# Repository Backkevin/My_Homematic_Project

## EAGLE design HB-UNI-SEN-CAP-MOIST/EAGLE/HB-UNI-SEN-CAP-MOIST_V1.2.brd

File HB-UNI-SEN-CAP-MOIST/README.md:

# HB-UNI-SEN-CAP-MOIST

+ HB-UNI-SEN-CAP-MOIST
    + V1.2
		* Work 75%
		* 230VAC Version
		* Partlist not OK
	+ V0.5
		* Work 25%
		* Solar Version
		* Partlist not OK
	+ Work in progress !
>

### Partslist 230VAC Version
                    
  Part Name   |      PIC      |   Part Info   | Part Quantity |   Part Link 
------------- | ------------- | ------------- | ------------- | -------------
Arduino||Arduino Pro Mini 8Mhz 3.3V|1|[Links](https://de.aliexpress.com/item/32863952987.html?spm=a2g0s.9042311.0.0.27424c4d2YDzey)
CC1101||CC1101 Funkmodul|1|[Links](https://de.aliexpress.com/item/32924239954.html?spm=a2g0s.9042311.0.0.27424c4dO9ofu2)
Config,S1 - S4||Taster 6x6|5|[Links](https://de.aliexpress.com/item/32912263133.html?spm=a2g0s.9042311.0.0.2cb44c4dtuowdv)
LED1||LED 3mm|1|[Links](https://de.aliexpress.com/item/32844298998.html?spm=a2g0s.9042311.0.0.27424c4dBW9kvr)
HLK-5M05||HLK-PM01|1|[Links](https://de.aliexpress.com/item/32705471039.html?spm=a2g0s.9042311.0.0.2cb44c4dtuowdv)
F1,F2||Sicherungshalter|2|[Links](https://de.aliexpress.com/item/32817849786.html?spm=a2g0o.productlist.0.0.260073beDSkClD&algo_pvid=51b52a6f-dc94-4152-9721-98bffea40076&algo_expid=51b52a6f-dc94-4152-9721-98bffea40076-1&btsid=c94e558f-368d-470b-a49c-61c69230d3d9&ws_ab_test=searchweb0_0,searchweb201602_2,searchweb201603_52)
R1 - R5||470 Ohm Widerstand|5|[Links](https://de.aliexpress.com/item/32475181535.html?spm=a2g0o.productlist.0.0.d4fa8034p2AKck&s=p&algo_pvid=4976c9e3-6165-4df4-b127-6d9845fdbe12&algo_expid=4976c9e3-6165-4df4-b127-6d9845fdbe12-1&btsid=7a52ff49-9ff4-47d2-965f-007ad481e8b7&ws_ab_test=searchweb0_0,searchweb201602_2,searchweb201603_52)
230V,S1 - S4||Wannenstecker für AKL 249, 2-pol, RM5,08|5|[Links](https://www.reichelt.de/wannenstecker-fuer-akl-249-2-pol-rm5-08-akl-230-02-p36701.html?)
RL1 - RL4||Wannenstecker für AKL 249, 3-pol, RM5,08|4|[Links](https://www.reichelt.de/wannenstecker-fuer-akl-249-3-pol-rm5-08-akl-230-03-p36702.html?)
Arduino||Pin Header Streifen 12 Pin|2|[Links](https://de.aliexpress.com/item/32904918519.html?spm=a2g0s.9042311.0.0.27424c4dCsKCBi)
CC1101||Stiftleiste 20 polig, vergoldet, Raster 2,00mm|1|[Links](https://secure.reichelt.com/lu/de/stiftleiste-20-pol-vergoldet-bkl-10120400-p235635.html?)
C1||50V10UF|1|[Links](https://de.aliexpress.com/item/32741687066.html?spm=a2g0o.productlist.0.0.4d225216N68Cr1&algo_pvid=dbcb75f4-e623-4355-8aa4-ccd3a7b65d32&algo_expid=dbcb75f4-e623-4355-8aa4-ccd3a7b65d32-3&btsid=a9b8176e-1372-45d7-a781-8d3fc9fab8e5&ws_ab_test=searchweb0_0,searchweb201602_2,searchweb201603_52)
Arduino||Jumper|1|[Links](https://de.aliexpress.com/item/32873263301.html?spm=a2g0o.productlist.0.0.18ea263dluRsmQ&algo_pvid=b495ebad-e4de-4809-a086-8143c1f9f12b&algo_expid=b495ebad-e4de-4809-a086-8143c1f9f12b-2&btsid=53bb7c29-6fd7-4471-b8c4-bc2766b36d10&ws_ab_test=searchweb0_0,searchweb201602_2,searchweb201603_52)
-|-|-|-
-||Feuchtigkeit Sensor|7|[Links](https://de.aliexpress.com/item/32892951369.html?spm=a2g0s.9042311.0.0.27424c4dkyqylL)
OPTIONAL||FT232RL USB zu TTL Serielle Adapter|1|[Links](https://de.aliexpress.com/item/32846166237.html?spm=a2g0s.9042311.0.0.27424c4dQGznlY)

>

### Partslist Solar Version
                    
  Part Name   |      PIC      |   Part Info   | Part Quantity |   Part Link 
------------- | ------------- | ------------- | ------------- | -------------
-||Arduino Pro Mini 8Mhz 3.3V|1|[Links](https://de.aliexpress.com/item/32863952987.html?spm=a2g0s.9042311.0.0.27424c4d2YDzey)
-||CC1101 Funkmodul|1|[Links](https://de.aliexpress.com/item/32924239954.html?spm=a2g0s.9042311.0.0.27424c4dO9ofu2)
Config||Taster 6x6|1|[Links](https://de.aliexpress.com/item/32912263133.html?spm=a2g0s.9042311.0.0.2cb44c4dtuowdv)
LED1||LED 3mm|1|[Links](https://de.aliexpress.com/item/32844298998.html?spm=a2g0s.9042311.0.0.27424c4dBW9kvr)
R1||470 Ohm Widerstand|1|[Links]()
Arduino||Pin Header Streifen 12 Pin|2|[Links](https://de.aliexpress.com/item/32904918519.html?spm=a2g0s.9042311.0.0.27424c4dCsKCBi)
CC1101||Stiftleiste 20 polig, vergoldet, Raster 2,00mm|1|[Links](https://secure.reichelt.com/lu/de/stiftleiste-20-pol-vergoldet-bkl-10120400-p235635.html?)
C1||50V10UF|1|[Links](https://de.aliexpress.com/item/32741687066.html?spm=a2g0o.productlist.0.0.4d225216N68Cr1&algo_pvid=dbcb75f4-e623-4355-8aa4-ccd3a7b65d32&algo_expid=dbcb75f4-e623-4355-8aa4-ccd3a7b65d32-3&btsid=a9b8176e-1372-45d7-a781-8d3fc9fab8e5&ws_ab_test=searchweb0_0,searchweb201602_2,searchweb201603_52)
Sabotage,Arduino||Jumper|1|[Links](https://de.aliexpress.com/item/32873263301.html?spm=a2g0o.productlist.0.0.18ea263dluRsmQ&algo_pvid=b495ebad-e4de-4809-a086-8143c1f9f12b&algo_expid=b495ebad-e4de-4809-a086-8143c1f9f12b-2&btsid=53bb7c29-6fd7-4471-b8c4-bc2766b36d10&ws_ab_test=searchweb0_0,searchweb201602_2,searchweb201603_52)
-||Ladegerät 5V|1|[Links](https://de.aliexpress.com/item/32816412117.html?spm=a2g0s.9042311.0.0.75df4c4dhlR1XP)
-||LiPo Protect|1|[Links](https://de.aliexpress.com/item/32816412117.html?spm=a2g0s.9042311.0.0.75df4c4dhlR1XP)
-||Lipo Batterie 3,7 V 800 mah|1|[Links](https://de.aliexpress.com/item/32884273792.html?spm=a2g0s.9042311.0.0.27424c4dkyqylL)
-||Solar Panel 6 V 2 W 0.35A|1|[Links](https://de.aliexpress.com/item/32955737209.html?spm=a2g0s.9042311.0.0.27424c4dBO3PxC)
-||SMA buchse Adapter|1|[Links](https://de.aliexpress.com/item/32876812319.html?spm=a2g0s.9042311.0.0.27424c4dkyqylL)
-|-|-|-
-||Feuchtigkeit Sensor|7|[Links](https://de.aliexpress.com/item/32892951369.html?spm=a2g0s.9042311.0.0.27424c4dkyqylL)
OPTIONAL||FT232RL USB zu TTL Serielle Adapter|1|[Links](https://de.aliexpress.com/item/32846166237.html?spm=a2g0s.9042311.0.0.27424c4dQGznlY)

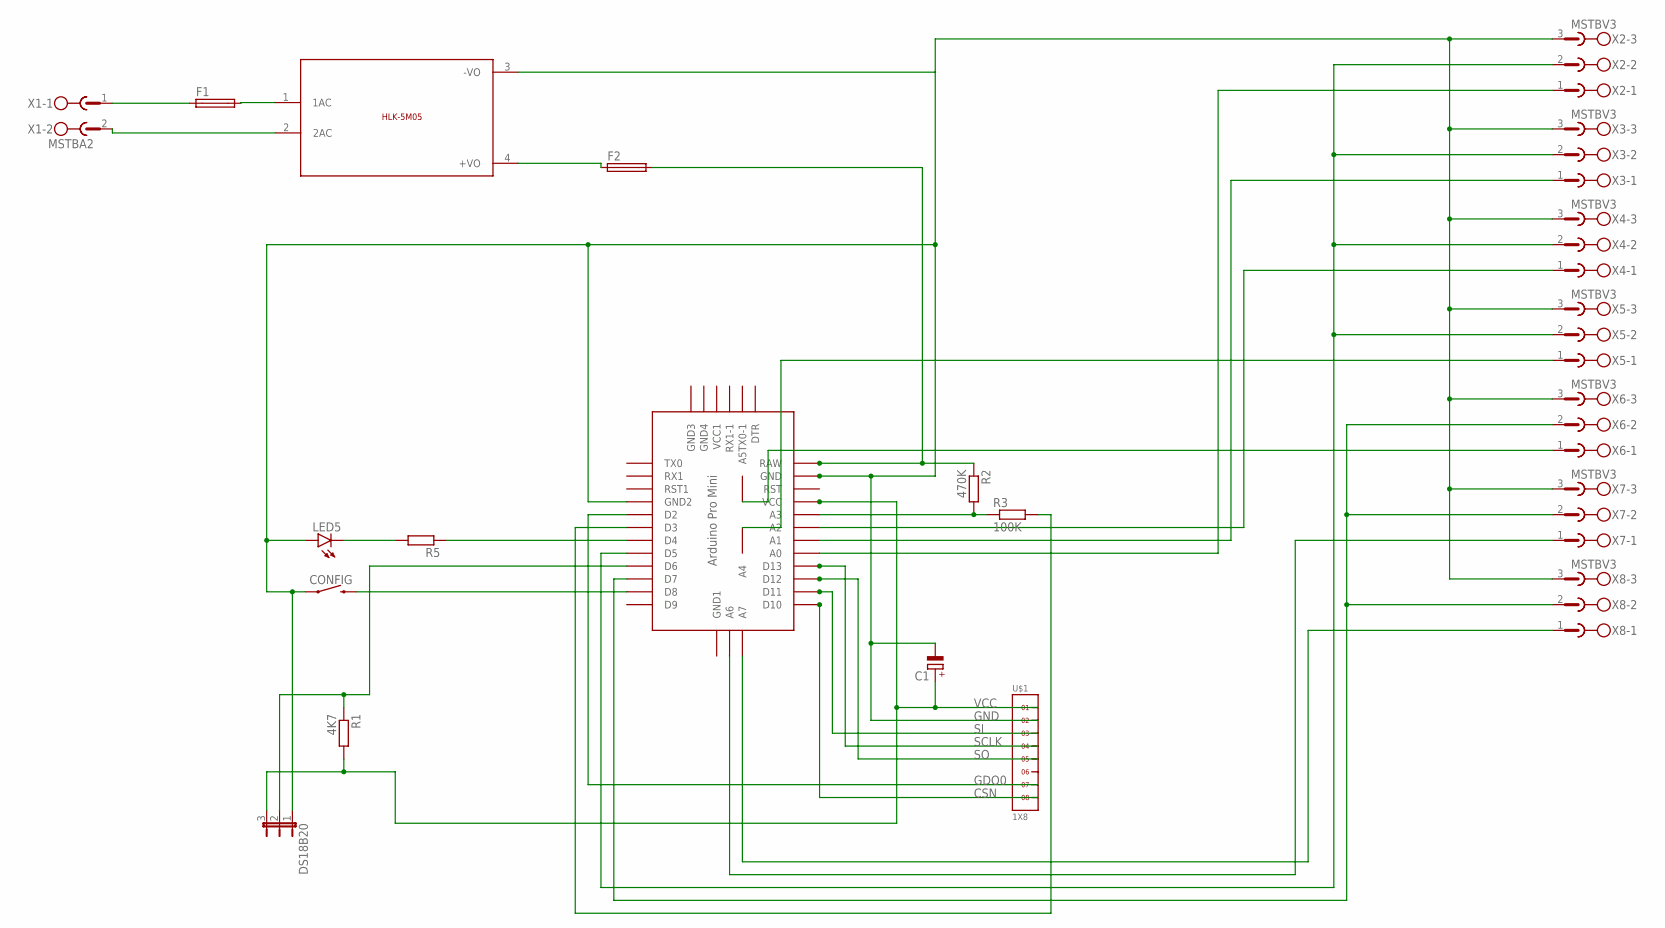
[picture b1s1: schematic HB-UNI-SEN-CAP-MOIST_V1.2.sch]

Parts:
C1: CPOL-EUE2.5-5; E2,5-5
CONFIG: MOMENTARY-SWITCH-SPST-PTH-6.0MM-KIT; TACTILE_SWITCH_PTH_6.0MM_KIT
DS18B20: JP2E; JP2
F1, F2: SH22,5A
LED5: LED3MM
R1: 4K7; 0309/10
R2: 470K; 0309/10
R3: 100K; 0309/10
R5: R-EU_0309/10; 0309/10
U$1: 1X8
U$2: ABK-PRO-MINI
U$3: 5VDC/5W; HLK-5M05
X1: MSTBA2
X2, X3, X4, X5, X6, X7, X8: MSTBV3

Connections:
CSN: U$1.8, U$2.D10
GDO0: U$1.7, U$2.D2
GND: C1.-, CONFIG.1, DS18B20.1, LED5.A, U$1.2, U$2.GND, U$2.GND1 (GND2), U$3.3 (-VO), X2.3, X3.3, X4.3, X5.3, X6.3, X7.3, X8.3
unnamed: U$2.A0, X2.1
unnamed: U$2.A1, X3.1
unnamed: U$2.A2, X4.1
unnamed: U$2.A4, X5.1
unnamed: U$2.A5, X6.1
unnamed: U$2.A6, X7.1
unnamed: U$2.A7, X8.1
unnamed: U$2.D5, X2.2, X3.2, X4.2, X5.2
unnamed: F1.1, X1.1
unnamed: F2.1, U$3.4 (+VO)
unnamed: U$3.2 (2AC), X1.2
unnamed: U$2.D7, X6.2, X7.2, X8.2
unnamed: DS18B20.2, R1.1, U$2.D6
unnamed: R2.2, R3.1, U$2.A3
unnamed: R3.2, U$2.D3
unnamed: CONFIG.3 (2), U$2.D8
unnamed: R5.1, U$2.D4
unnamed: LED5.K (C), R5.2
unnamed: F1.2, U$3.1 (1AC)
unnamed: F2.2, R2.1, U$2.RAW
SCLK: U$1.4, U$2.D13
SI: U$1.3, U$2.D11
SO: U$1.5, U$2.D12
VCC: C1.+, DS18B20.3, R1.2, U$1.1, U$2.VCC

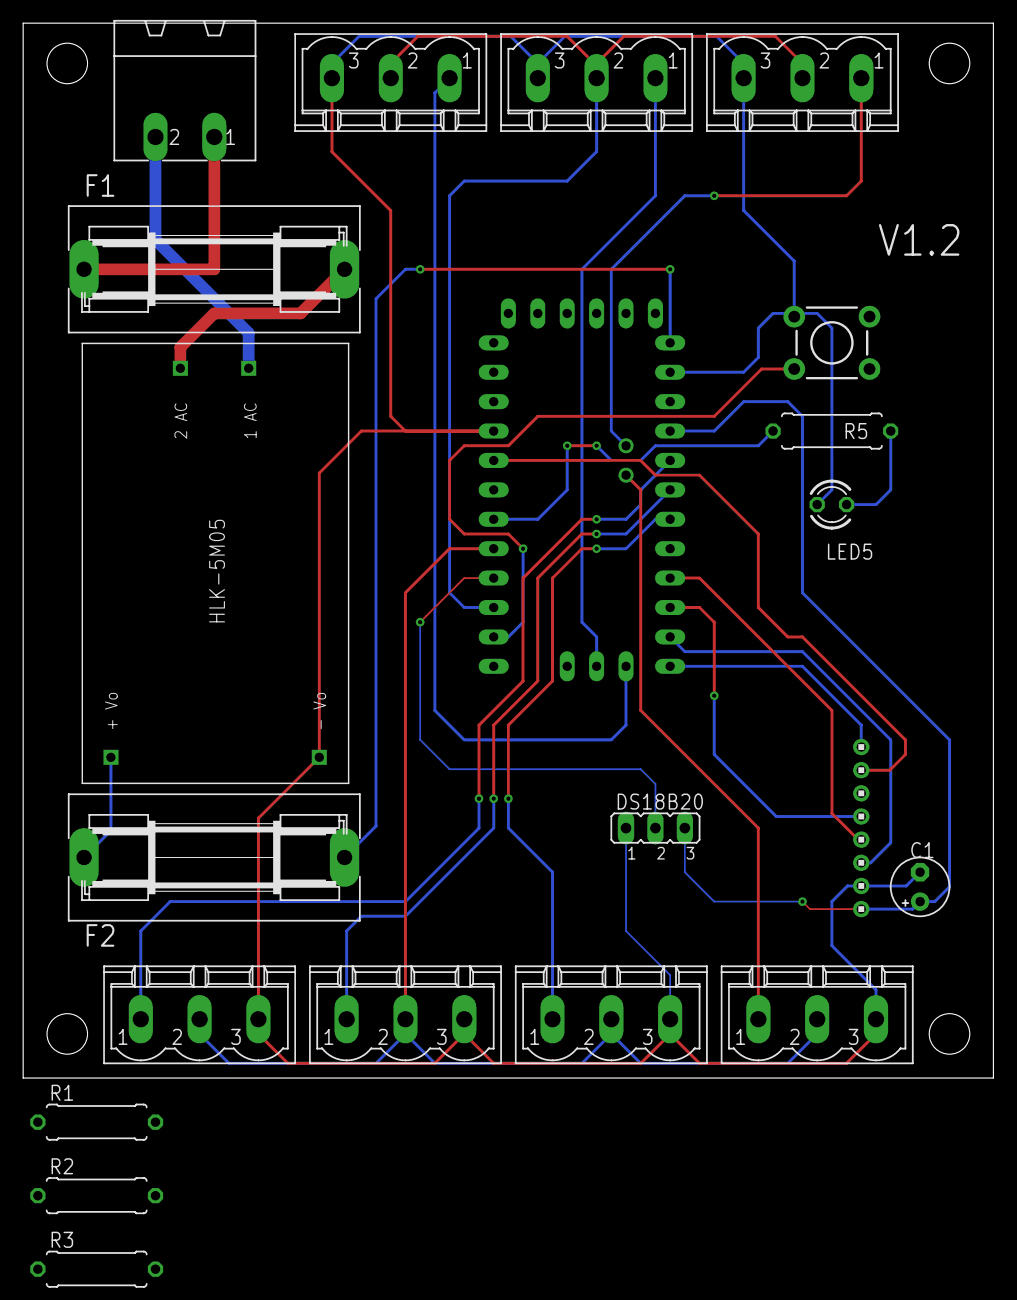
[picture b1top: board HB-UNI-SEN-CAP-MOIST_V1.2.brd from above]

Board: 2 copper layers, 83.8 x 91.1 mm, 21 parts (0 on the bottom side), 27 nets.

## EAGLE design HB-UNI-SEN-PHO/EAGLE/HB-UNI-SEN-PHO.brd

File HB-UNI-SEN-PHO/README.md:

# HB-UNI-SEN-PHO

+ HB-UNI-SEN-PHO
	+ V1.0
		* Work 25%
		* 230VAC Version
		* Partlist not OK
	+ Work in progress !
>

### Partslist 230VAC Version
                    
  Part Name   |      PIC      |   Part Info   | Part Quantity |   Part Link 
------------- | ------------- | ------------- | ------------- | -------------
Arduino||Arduino Pro Mini 8Mhz 3.3V|1|[Links](https://de.aliexpress.com/item/32863952987.html?spm=a2g0s.9042311.0.0.27424c4d2YDzey)
CC1101||CC1101 Funkmodul|1|[Links](https://de.aliexpress.com/item/32924239954.html?spm=a2g0s.9042311.0.0.27424c4dO9ofu2)
Config,S1 - S4||Taster 6x6|5|[Links](https://de.aliexpress.com/item/32912263133.html?spm=a2g0s.9042311.0.0.2cb44c4dtuowdv)
LED1 - LED5||LED 3mm|5|[Links](https://de.aliexpress.com/item/32844298998.html?spm=a2g0s.9042311.0.0.27424c4dBW9kvr)
HLK-5M05||HLK-PM01|1|[Links](https://de.aliexpress.com/item/32705471039.html?spm=a2g0s.9042311.0.0.2cb44c4dtuowdv)
F1,F2||Sicherungshalter|2|[Links](https://de.aliexpress.com/item/32817849786.html?spm=a2g0o.productlist.0.0.260073beDSkClD&algo_pvid=51b52a6f-dc94-4152-9721-98bffea40076&algo_expid=51b52a6f-dc94-4152-9721-98bffea40076-1&btsid=c94e558f-368d-470b-a49c-61c69230d3d9&ws_ab_test=searchweb0_0,searchweb201602_2,searchweb201603_52)
R1 - R5||470 Ohm Widerstand|5|[Links](https://de.aliexpress.com/item/32475181535.html?spm=a2g0o.productlist.0.0.d4fa8034p2AKck&s=p&algo_pvid=4976c9e3-6165-4df4-b127-6d9845fdbe12&algo_expid=4976c9e3-6165-4df4-b127-6d9845fdbe12-1&btsid=7a52ff49-9ff4-47d2-965f-007ad481e8b7&ws_ab_test=searchweb0_0,searchweb201602_2,searchweb201603_52)
230V,S1 - S4||Wannenstecker für AKL 249, 2-pol, RM5,08|5|[Links](https://www.reichelt.de/wannenstecker-fuer-akl-249-2-pol-rm5-08-akl-230-02-p36701.html?)
RL1 - RL4||Wannenstecker für AKL 249, 3-pol, RM5,08|4|[Links](https://www.reichelt.de/wannenstecker-fuer-akl-249-3-pol-rm5-08-akl-230-03-p36702.html?)
RL1 - RL4||relais srd-05vdc|4|[Links](https://de.aliexpress.com/item/32695798177.html?spm=a2g0o.productlist.0.0.46db7659cuB4fB&algo_pvid=f16bd12e)
Arduino||Pin Header Streifen 12 Pin|2|[Links](https://de.aliexpress.com/item/32904918519.html?spm=a2g0s.9042311.0.0.27424c4dCsKCBi)
CC1101||Stiftleiste 20 polig, vergoldet, Raster 2,00mm|1|[Links](https://secure.reichelt.com/lu/de/stiftleiste-20-pol-vergoldet-bkl-10120400-p235635.html?)
ULN2803||ULN2803A|1|[Links](https://de.aliexpress.com/item/32881616806.html?spm=a2g0o.productlist.0.0.27805012dPDPf4&algo_pvid=2ce275e5-5ca6-4441-a1e3-fb3df6923537&algo_expid=2ce275e5-5ca6-4441-a1e3-fb3df6923537-0&btsid=14cad76a-3ab1-4af8-af47-443eb0bf5dae&ws_ab_test=searchweb0_0,searchweb201602_2,searchweb201603_52)
C1||50V10UF|1|[Links](https://de.aliexpress.com/item/32741687066.html?spm=a2g0o.productlist.0.0.4d225216N68Cr1&algo_pvid=dbcb75f4-e623-4355-8aa4-ccd3a7b65d32&algo_expid=dbcb75f4-e623-4355-8aa4-ccd3a7b65d32-3&btsid=a9b8176e-1372-45d7-a781-8d3fc9fab8e5&ws_ab_test=searchweb0_0,searchweb201602_2,searchweb201603_52)
Sabotage,Arduino||Jumper|1|[Links](https://de.aliexpress.com/item/32873263301.html?spm=a2g0o.productlist.0.0.18ea263dluRsmQ&algo_pvid=b495ebad-e4de-4809-a086-8143c1f9f12b&algo_expid=b495ebad-e4de-4809-a086-8143c1f9f12b-2&btsid=53bb7c29-6fd7-4471-b8c4-bc2766b36d10&ws_ab_test=searchweb0_0,searchweb201602_2,searchweb201603_52)
PH||PH 0-14 Wert Erkennung Regler Sensor|1|[Links](https://de.aliexpress.com/item/32995322213.html?spm=a2g0s.9042311.0.0.27424c4durraPx)
O|| Gelöst Sauerstoff Sensor Meter Kit, 3,3 ~ 5,5 V|1|[Links](https://de.aliexpress.com/item/32833443811.html?spm=a2g0x.search0306.3.67.2d033415plncNk&ws_ab_test=searchweb0_0,searchweb201602_0_10084_10083_10821_10887_10307_321_453_322_454_10618_536_10065_317_537_10068_319_10059_10103_10884_10696_10303_10820_10302,searchweb201603_0,ppcSwitch_0&algo_pvid=8e616f7e-9e8e-4157-afdd-3e1318ff78a1&algo_expid=8e616f7e-9e8e-4157-afdd-3e1318ff78a1-11)
-|-|-|-|-
OPTIONAL||Kalibrierung Lösung ph4.00/6,86/9,18|1|[Links](https://de.aliexpress.com/item/32785292290.html?spm=a2g0s.9042311.0.0.27424c4durraPx)
OPTIONAL||FT232RL USB zu TTL Serielle Adapter|1|[Links](https://de.aliexpress.com/item/32846166237.html?spm=a2g0s.9042311.0.0.27424c4dQGznlY)

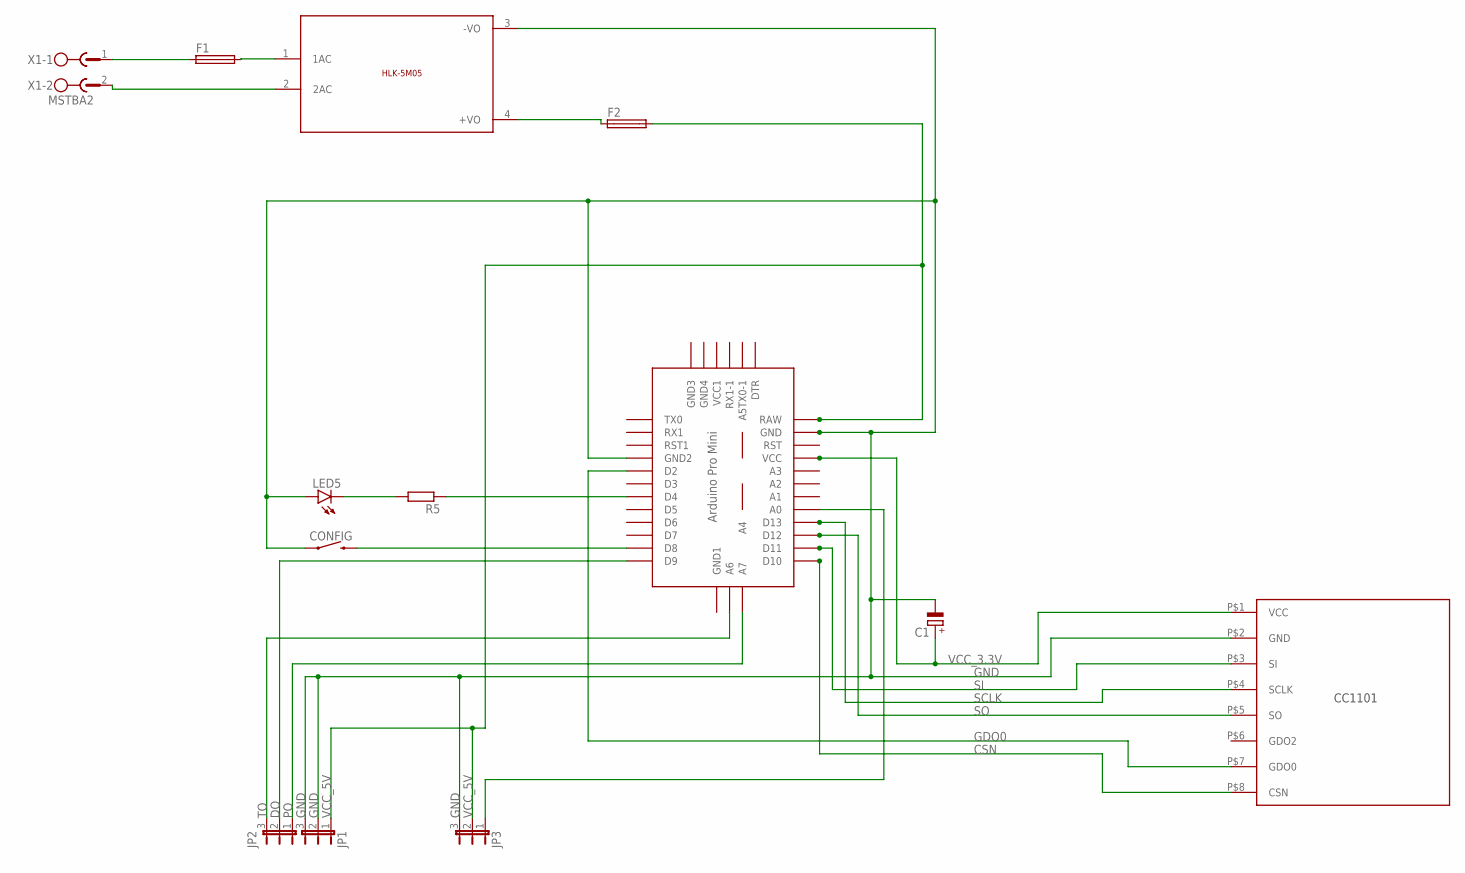
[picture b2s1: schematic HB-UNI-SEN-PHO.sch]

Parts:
C1: CPOL-EUE2.5-5; E2,5-5
CONFIG: MOMENTARY-SWITCH-SPST-PTH-6.0MM-KIT; TACTILE_SWITCH_PTH_6.0MM_KIT
F1, F2: SH22,5A
JP1, JP2, JP3: JP2E; JP2
LED5: LED3MM
R5: R-EU_0309/10; 0309/10
U$2: ABK-PRO-MINI
U$3: 5VDC/5W; HLK-5M05
U$4: CC1101
X1: MSTBA2

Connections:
CSN: U$2.D10, U$4.P$8 (CSN)
DO: JP2.2, U$2.D9
GDO0: U$2.D2, U$4.P$7 (GDO0)
GND: C1.-, CONFIG.1, JP1.2, JP1.3, JP3.3, LED5.A, U$2.GND, U$2.GND1 (GND2), U$3.3 (-VO), U$4.P$2 (GND)
unnamed: JP3.1, U$2.A0
unnamed: F1.1, X1.1
unnamed: F2.1, U$3.4 (+VO)
unnamed: U$3.2 (2AC), X1.2
unnamed: CONFIG.3 (2), U$2.D8
unnamed: R5.1, U$2.D4
unnamed: LED5.K (C), R5.2
unnamed: F1.2, U$3.1 (1AC)
PO: JP2.1, U$2.A7
SCLK: U$2.D13, U$4.P$4 (SCLK)
SI: U$2.D11, U$4.P$3 (SI)
SO: U$2.D12, U$4.P$5 (SO)
TO: JP2.3, U$2.A6
VCC_3.3V: C1.+, U$2.VCC, U$4.P$1 (VCC)
VCC_5V: F2.2, JP1.1, JP3.2, U$2.RAW

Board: 2 copper layers, 13 parts (0 on the bottom side), 19 nets, no tracks yet.

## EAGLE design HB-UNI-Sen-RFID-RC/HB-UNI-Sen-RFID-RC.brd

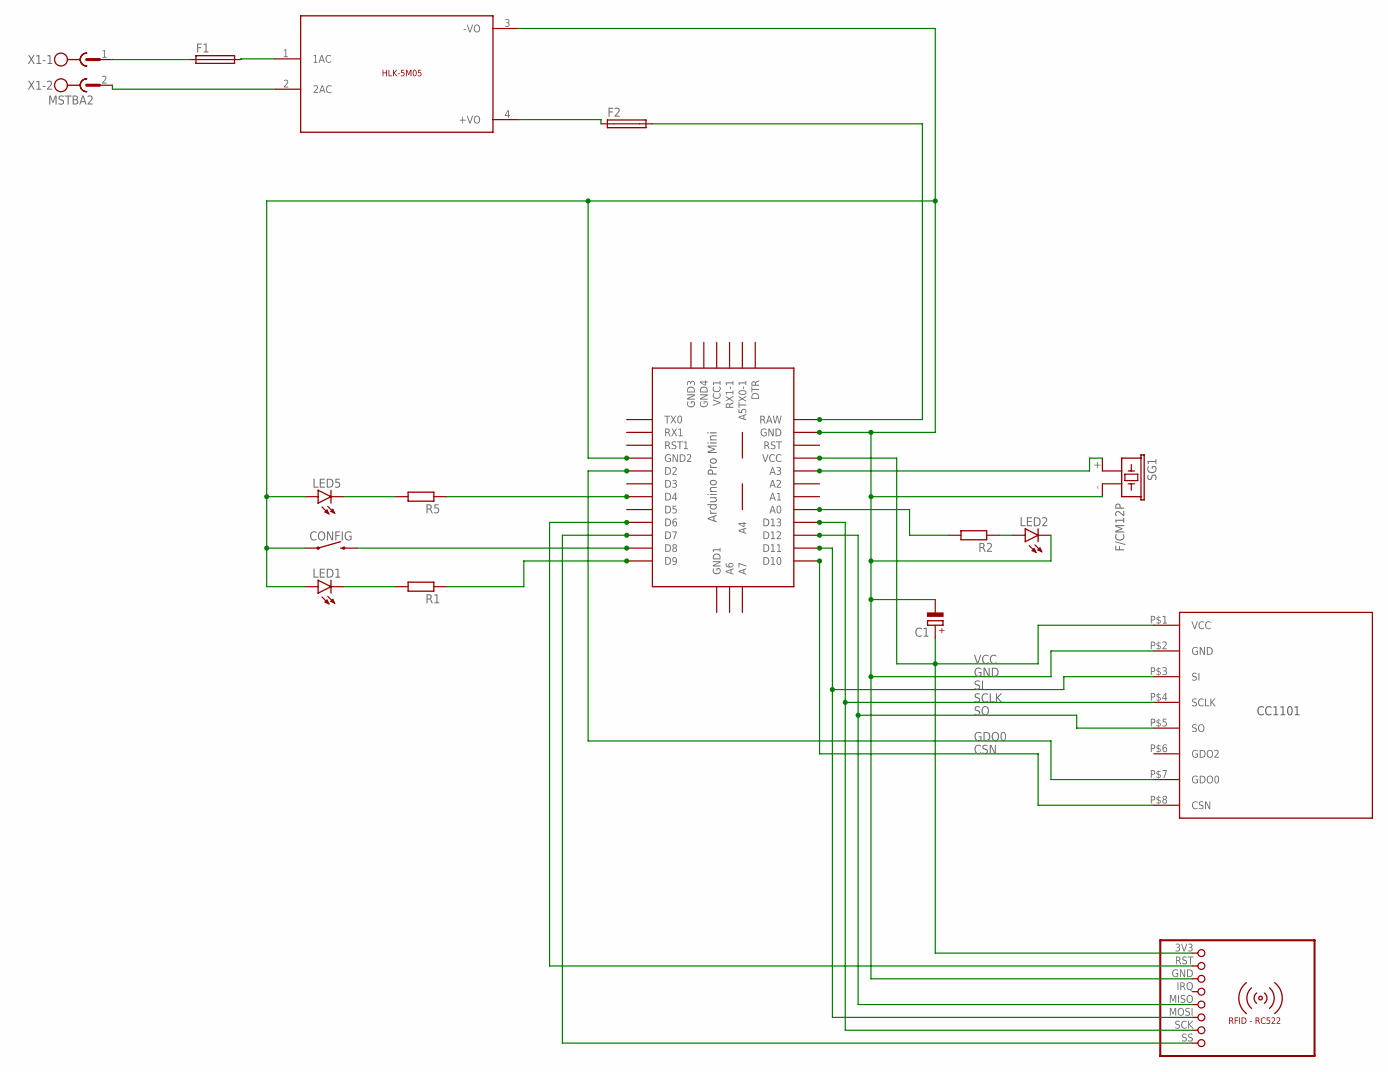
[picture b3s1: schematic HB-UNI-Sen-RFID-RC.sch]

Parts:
C1: CPOL-EUE2.5-5; E2,5-5
CONFIG: MOMENTARY-SWITCH-SPST-PTH-6.0MM-KIT; TACTILE_SWITCH_PTH_6.0MM_KIT
F1, F2: SH22,5A
LED1, LED2, LED5: LED3MM
M1: RFID-RC522
R1, R2, R5: R-EU_0309/10; 0309/10
SG1: F/CM12P
U$1: CC1101
U$2: ABK-PRO-MINI
U$3: 5VDC/5W; HLK-5M05
X1: MSTBA2

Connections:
CSN: U$1.P$8 (CSN), U$2.D10
GDO0: U$1.P$7 (GDO0), U$2.D2
GND: C1.-, CONFIG.1, LED1.A, LED2.K (C), LED5.A, M1.GND (3), SG1.- (2), U$1.P$2 (GND), U$2.GND, U$2.GND1 (GND2), U$3.3 (-VO)
unnamed: M1.SS (8), U$2.D7
unnamed: M1.RST (2), U$2.D6
unnamed: LED1.K (C), R1.2
unnamed: R1.1, U$2.D9
unnamed: SG1.+ (1), U$2.A3
unnamed: LED2.A, R2.1
unnamed: R2.2, U$2.A0
unnamed: F1.1, X1.1
unnamed: F2.1, U$3.4 (+VO)
unnamed: U$3.2 (2AC), X1.2
unnamed: CONFIG.3 (2), U$2.D8
unnamed: R5.1, U$2.D4
unnamed: LED5.K (C), R5.2
unnamed: F1.2, U$3.1 (1AC)
unnamed: F2.2, U$2.RAW
SCLK: M1.SCK (7), U$1.P$4 (SCLK), U$2.D13
SI: M1.MOSI (6), U$1.P$3 (SI), U$2.D11
SO: M1.MISO (5), U$1.P$5 (SO), U$2.D12
VCC: C1.+, M1.3V3 (1), U$1.P$1 (VCC), U$2.VCC

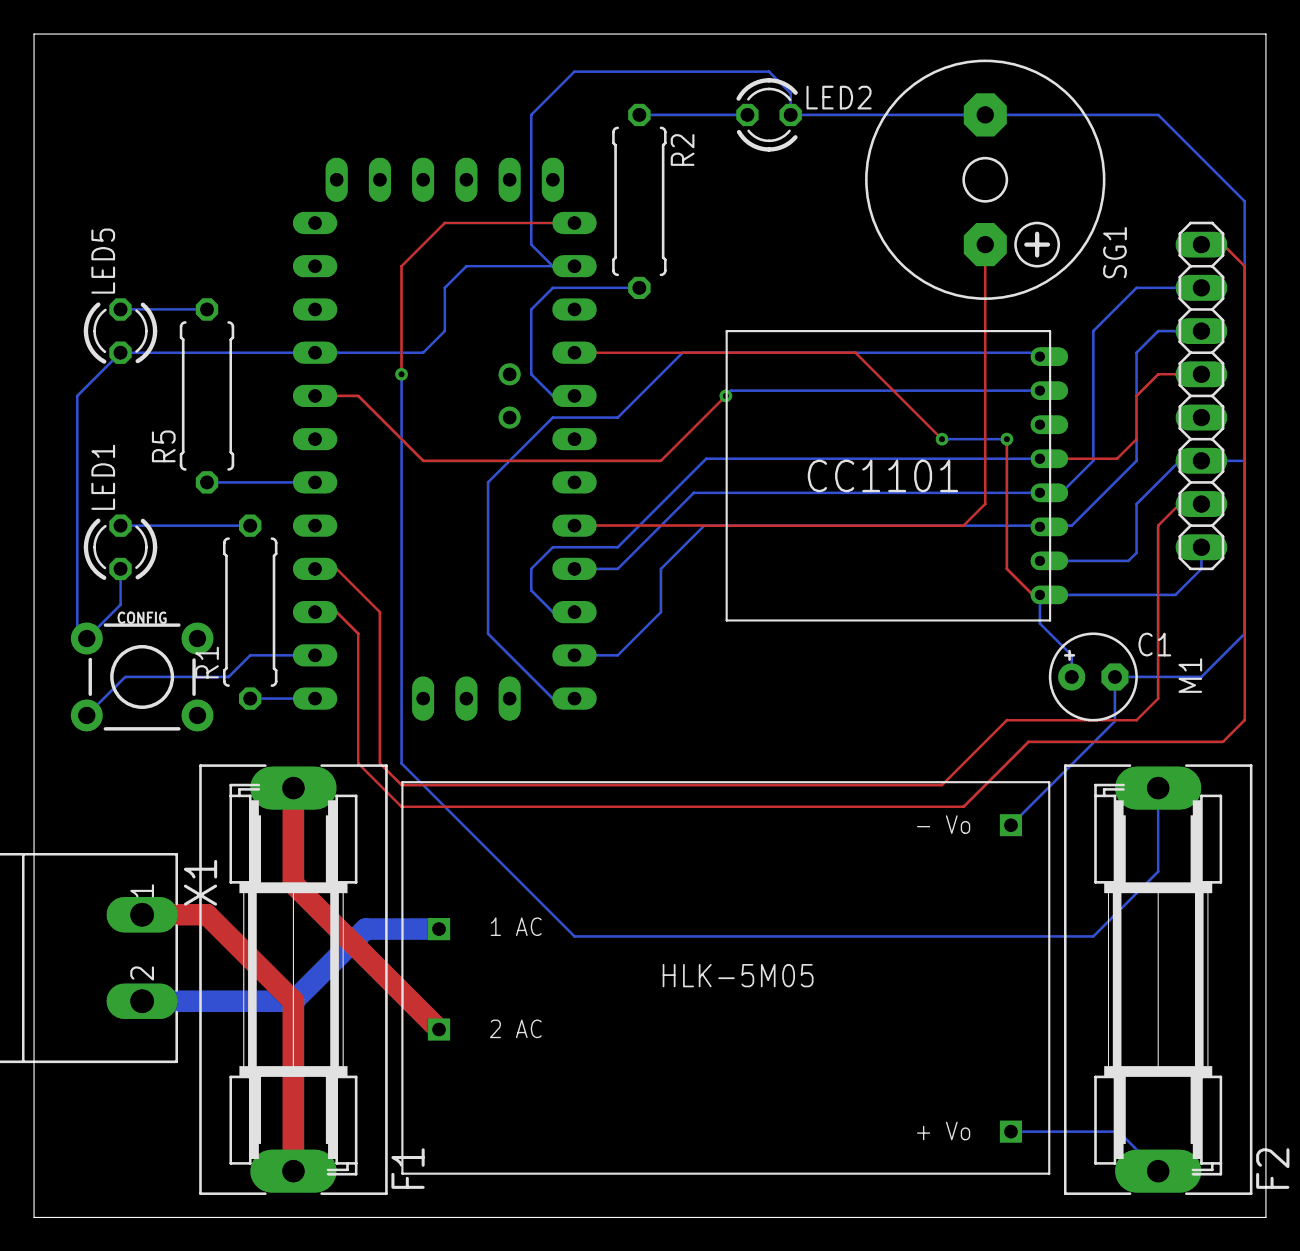
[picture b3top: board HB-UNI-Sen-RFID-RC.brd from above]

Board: 2 copper layers, 72.4 x 69.5 mm, 16 parts (0 on the bottom side), 22 nets.

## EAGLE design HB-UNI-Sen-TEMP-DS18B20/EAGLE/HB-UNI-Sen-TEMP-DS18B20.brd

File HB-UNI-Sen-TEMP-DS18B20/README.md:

# HB-UNI-Sen-TEMP-DS18B20

+ HB-UNI-Sen-TEMP-DS18B20
	+ V1.0
		* Work 75%
		* 230VAC Version
		* Partlist not OK
	+ Work in progress !
>

### Partslist 230VAC Version
                    
  Part Name   |      PIC      |   Part Info   | Part Quantity |   Part Link 
------------- | ------------- | ------------- | ------------- | -------------
Arduino||Arduino Pro Mini 8Mhz 3.3V|1|[Links](https://de.aliexpress.com/item/32863952987.html?spm=a2g0s.9042311.0.0.27424c4d2YDzey)
CC1101||CC1101 Funkmodul|1|[Links](https://de.aliexpress.com/item/32924239954.html?spm=a2g0s.9042311.0.0.27424c4dO9ofu2)
Config,S1 - S4||Taster 6x6|5|[Links](https://de.aliexpress.com/item/32912263133.html?spm=a2g0s.9042311.0.0.2cb44c4dtuowdv)
LED1 - LED5||LED 3mm|5|[Links](https://de.aliexpress.com/item/32844298998.html?spm=a2g0s.9042311.0.0.27424c4dBW9kvr)
HLK-5M05||HLK-PM01|1|[Links](https://de.aliexpress.com/item/32705471039.html?spm=a2g0s.9042311.0.0.2cb44c4dtuowdv)
F1,F2||Sicherungshalter|2|[Links](https://de.aliexpress.com/item/32817849786.html?spm=a2g0o.productlist.0.0.260073beDSkClD&algo_pvid=51b52a6f-dc94-4152-9721-98bffea40076&algo_expid=51b52a6f-dc94-4152-9721-98bffea40076-1&btsid=c94e558f-368d-470b-a49c-61c69230d3d9&ws_ab_test=searchweb0_0,searchweb201602_2,searchweb201603_52)
R1 - R5||470 Ohm Widerstand|5|[Links](https://de.aliexpress.com/item/32475181535.html?spm=a2g0o.productlist.0.0.d4fa8034p2AKck&s=p&algo_pvid=4976c9e3-6165-4df4-b127-6d9845fdbe12&algo_expid=4976c9e3-6165-4df4-b127-6d9845fdbe12-1&btsid=7a52ff49-9ff4-47d2-965f-007ad481e8b7&ws_ab_test=searchweb0_0,searchweb201602_2,searchweb201603_52)
230V,S1 - S4||Wannenstecker für AKL 249, 2-pol, RM5,08|5|[Links](https://www.reichelt.de/wannenstecker-fuer-akl-249-2-pol-rm5-08-akl-230-02-p36701.html?)
RL1 - RL4||Wannenstecker für AKL 249, 3-pol, RM5,08|4|[Links](https://www.reichelt.de/wannenstecker-fuer-akl-249-3-pol-rm5-08-akl-230-03-p36702.html?)
Arduino||Pin Header Streifen 12 Pin|2|[Links](https://de.aliexpress.com/item/32904918519.html?spm=a2g0s.9042311.0.0.27424c4dCsKCBi)
CC1101||Stiftleiste 20 polig, vergoldet, Raster 2,00mm|1|[Links](https://secure.reichelt.com/lu/de/stiftleiste-20-pol-vergoldet-bkl-10120400-p235635.html?)
C1||50V10UF|1|[Links](https://de.aliexpress.com/item/32741687066.html?spm=a2g0o.productlist.0.0.4d225216N68Cr1&algo_pvid=dbcb75f4-e623-4355-8aa4-ccd3a7b65d32&algo_expid=dbcb75f4-e623-4355-8aa4-ccd3a7b65d32-3&btsid=a9b8176e-1372-45d7-a781-8d3fc9fab8e5&ws_ab_test=searchweb0_0,searchweb201602_2,searchweb201603_52)
Sabotage,Arduino||Jumper|1|[Links](https://de.aliexpress.com/item/32873263301.html?spm=a2g0o.productlist.0.0.18ea263dluRsmQ&algo_pvid=b495ebad-e4de-4809-a086-8143c1f9f12b&algo_expid=b495ebad-e4de-4809-a086-8143c1f9f12b-2&btsid=53bb7c29-6fd7-4471-b8c4-bc2766b36d10&ws_ab_test=searchweb0_0,searchweb201602_2,searchweb201603_52)
DS18b20||Wasserdichte DS18b20|7|[Links](https://de.aliexpress.com/item/32968031204.html?spm=a2g0s.9042311.0.0.27424c4dtMYsf5)
-|-|-|-
OPTIONAL||FT232RL USB zu TTL Serielle Adapter|1|[Links](https://de.aliexpress.com/item/32846166237.html?spm=a2g0s.9042311.0.0.27424c4dQGznlY)

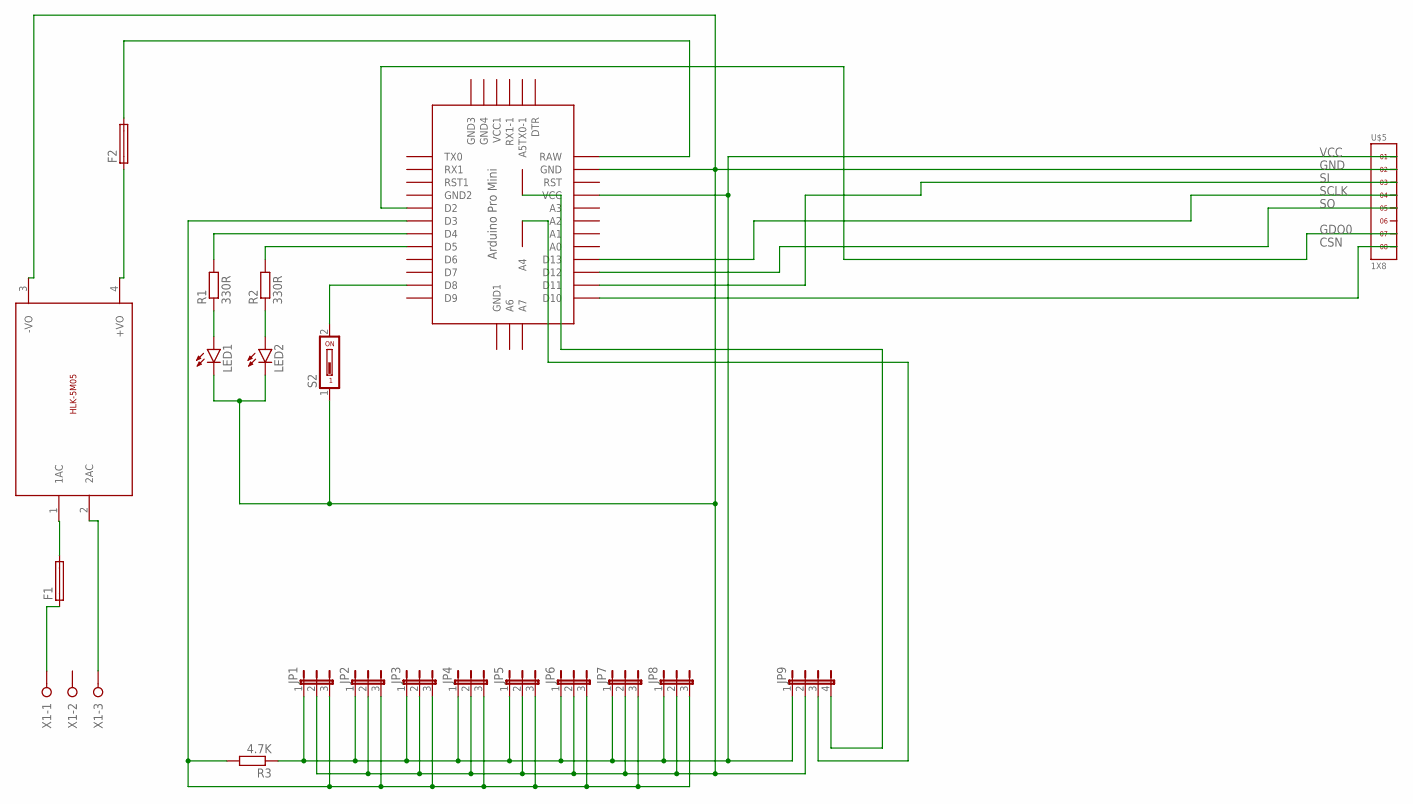
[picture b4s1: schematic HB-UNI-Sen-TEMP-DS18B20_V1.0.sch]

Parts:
F1, F2: GSH15
JP1, JP2, JP3, JP4, JP5, JP6, JP7, JP8: JP2W
JP9: JP4E; JP4
LED1, LED2: LED5MM
R1, R2: 330R; 0207/10
R3: 4.7K; 0207/10
S2: DS01; DS-01
U$1: ABK-PRO-MINI
U$3: 5VDC/5W; HLK-5M05
U$5: 1X8
X1: W237-3E

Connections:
CSN: U$1.D10, U$5.8
GDO0: U$1.D2, U$5.7
GND: JP1.2, JP2.2, JP3.2, JP4.2, JP5.2, JP6.2, JP7.2, JP8.2, JP9.2, LED1.K (C), LED2.K (C), S2.1, U$1.GND, U$3.3 (-VO), U$5.2
unnamed: F1.1, X1.1
unnamed: F2.1, U$3.4 (+VO)
unnamed: F1.2, U$3.1 (1AC)
unnamed: U$3.2 (2AC), X1.3
unnamed: JP1.3, JP2.3, JP3.3, JP4.3, JP5.3, JP6.3, JP7.3, JP8.3, R3.2, U$1.D3
unnamed: LED1.A, R1.1
unnamed: LED2.A, R2.1
unnamed: R1.2, U$1.D4
unnamed: R2.2, U$1.D5
unnamed: S2.2, U$1.D8
RAW: F2.2, U$1.RAW
SCL: JP9.4, U$1.A5
SCLK: U$1.D13, U$5.4
SDA: JP9.3, U$1.A4
SI: U$1.D11, U$5.3
SO: U$1.D12, U$5.5
VCC: JP1.1, JP2.1, JP3.1, JP4.1, JP5.1, JP6.1, JP7.1, JP8.1, JP9.1, R3.1, U$1.VCC, U$5.1

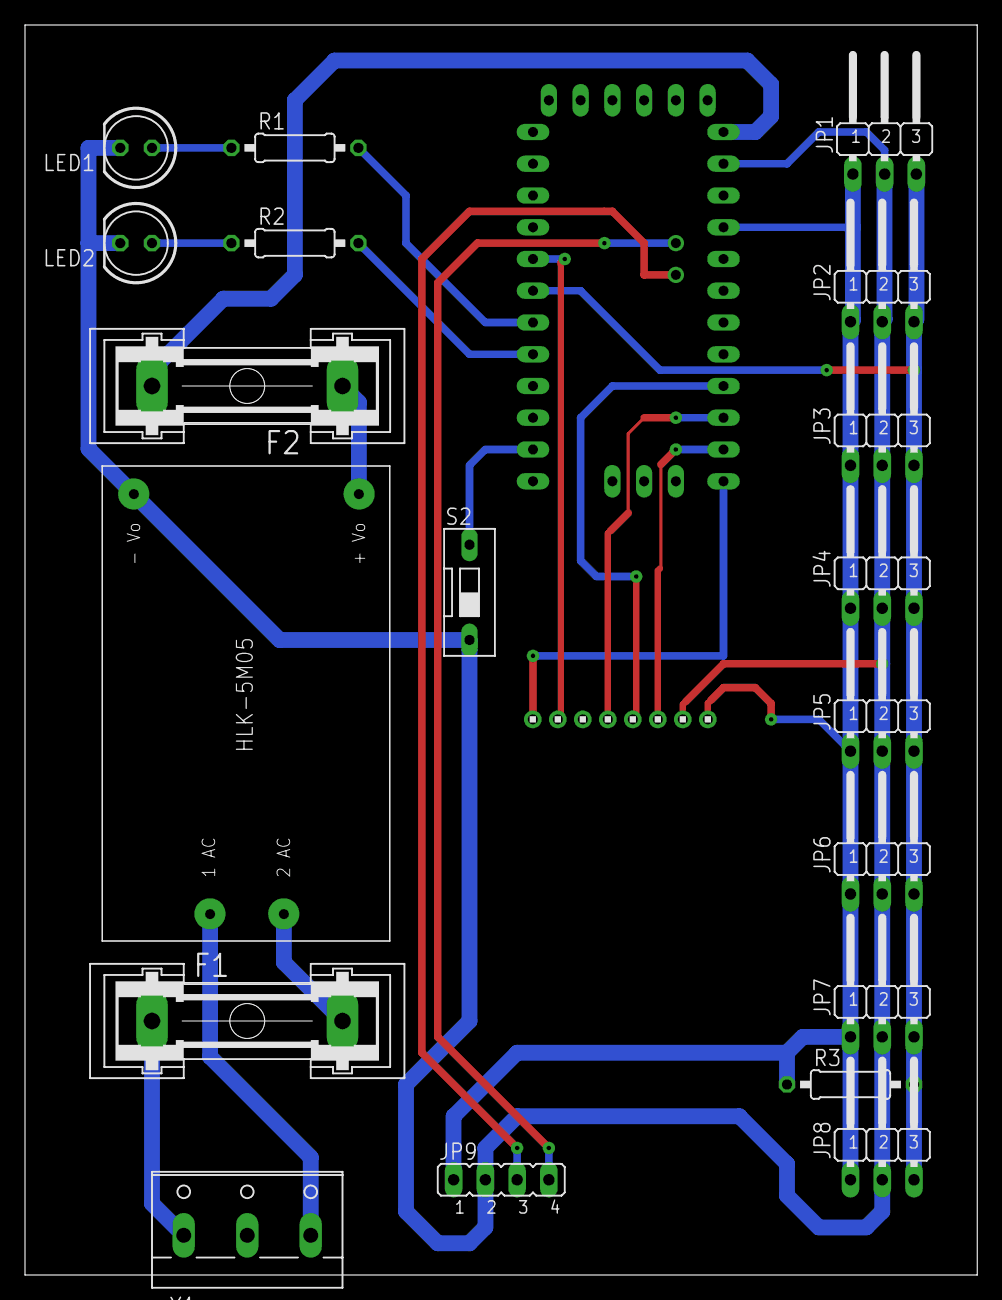
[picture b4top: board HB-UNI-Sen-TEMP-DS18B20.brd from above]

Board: 2 copper layers, 76.2 x 100.0 mm, 21 parts (0 on the bottom side), 20 nets.

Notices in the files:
parts and their libraries:
SparkFun-Switches: Licensing: Creative Commons ShareAlike 4.0 International - https://creativecommons.org/licenses/by-sa/4.0
